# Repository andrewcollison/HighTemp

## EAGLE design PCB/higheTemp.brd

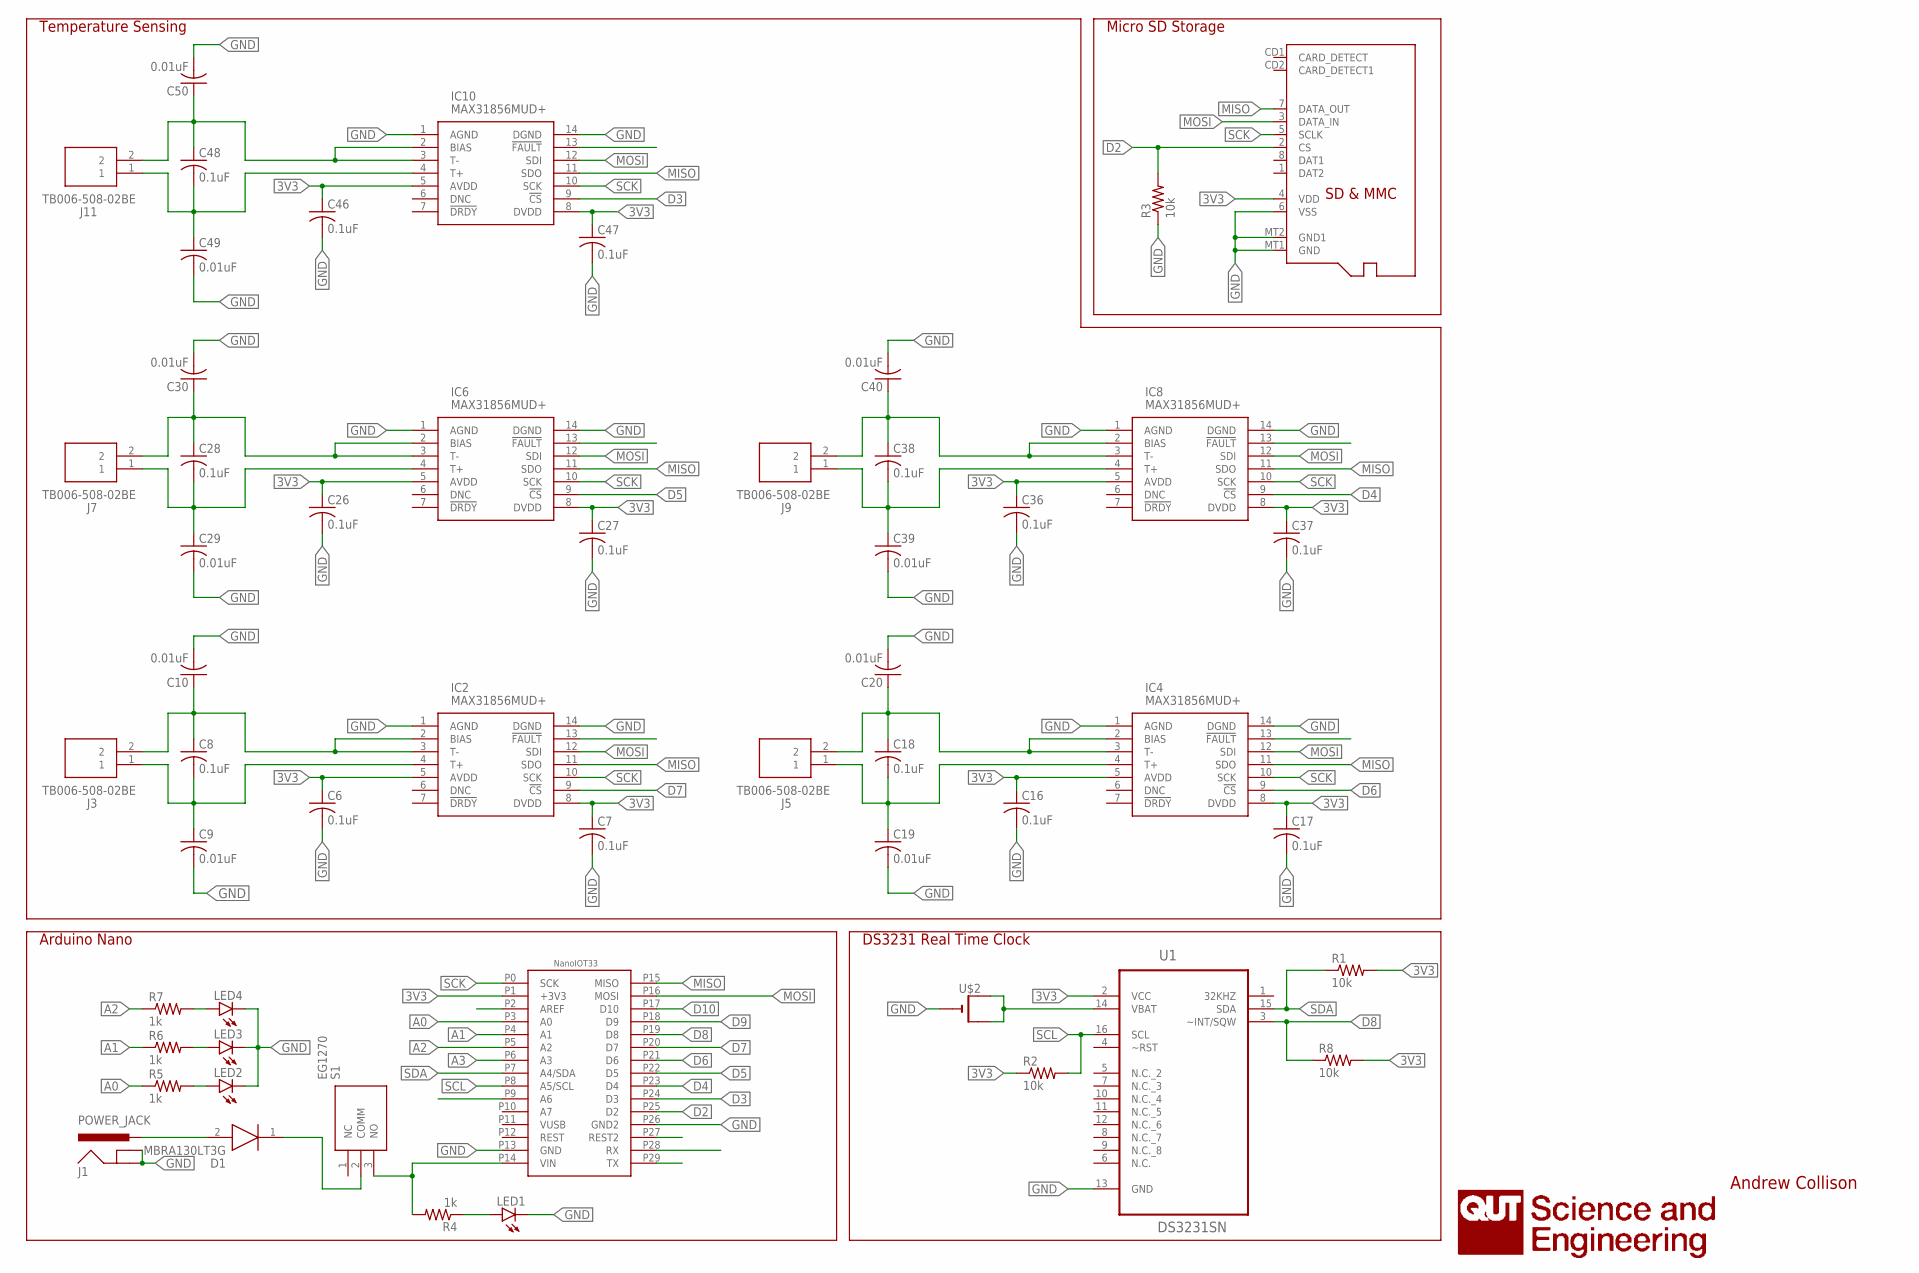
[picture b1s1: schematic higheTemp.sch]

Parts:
C6, C7, C8, C16, C17, C18, C26, C27, C28, C36, C37, C38, C46, C47, C48: 0.1uF; C0603
C9, C10, C19, C20, C29, C30, C39, C40, C49, C50: 0.01uF; C0603
D1: MBRA130LT3G; DIOM5226X220N
IC2, IC4, IC6, IC8, IC10: MAX31856MUD+; SOP65P640X110-14N
J1: POWER_JACK; POWER_JACK_PTH
J3, J5, J7, J9, J11: TB006-508-02BE; TB00650802BE
LED1, LED2, LED3, LED4: LEDCHIPLED_0805; CHIPLED_0805
R1, R2: 10k; R0603
R3, R8: 10k; R0805
R4, R5, R6, R7: 1k; R0603
S1: EG1270
U1: DS3231SN; SOIC127P1032X265-16N
U$1: NANO33IOT
U$2: CR1220SMT; CR1220-SMD
U$3: MICROSD

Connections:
3V3: C6.1, C7.1, C16.1, C17.1, C26.1, C27.1, C36.1, C37.1, C46.1, C47.1, IC2.5 (AVDD), IC2.8 (DVDD), IC4.5 (AVDD), IC4.8 (DVDD), IC6.5 (AVDD), IC6.8 (DVDD), IC8.5 (AVDD), IC8.8 (DVDD), IC10.5 (AVDD), IC10.8 (DVDD), R1.2, R2.1, R8.2, U1.2 (VCC), U$1.P1 (+3V3), U$3.4 (VDD)
A0: R5.1, U$1.P3 (A0)
A1: R6.1, U$1.P4 (A1)
A2: R7.1, U$1.P5 (A2)
A3: U$1.P6 (A3)
D2: R3.2, U$1.P25 (D2), U$3.2 (CS)
D3: IC10.9 (!CS), U$1.P24 (D3)
D4: IC8.9 (!CS), U$1.P23 (D4)
D5: IC6.9 (!CS), U$1.P22 (D5)
D6: IC4.9 (!CS), U$1.P21 (D6)
D7: IC2.9 (!CS), U$1.P20 (D7)
D8: R8.1, U1.3 (~INT/SQW), U$1.P19 (D8)
D9: U$1.P18 (D9)
D10: U$1.P17 (D10)
GND: C6.2, C7.2, C9.2, C10.2, C16.2, C17.2, C19.2, C20.2, C26.2, C27.2, C29.2, C30.2, C36.2, C37.2, C39.2, C40.2, C46.2, C47.2, C49.2, C50.2, IC2.1 (AGND), IC2.14 (DGND), IC4.1 (AGND), IC4.14 (DGND), IC6.1 (AGND), IC6.14 (DGND), IC8.1 (AGND), IC8.14 (DGND), IC10.1 (AGND), IC10.14 (DGND), J1.GND, J1.GNDBREAK, LED1.C, LED2.C, LED3.C, LED4.C, R3.1, U1.13 (GND), U$1.P13 (GND), U$1.P26 (GND2), U$2.-, U$3.6 (VSS), U$3.MT1 (GND), U$3.MT2 (GND1)
MISO: IC2.11 (SDO), IC4.11 (SDO), IC6.11 (SDO), IC8.11 (SDO), IC10.11 (SDO), U$1.P15 (MISO), U$3.7 (DATA_OUT)
MOSI: IC2.12 (SDI), IC4.12 (SDI), IC6.12 (SDI), IC8.12 (SDI), IC10.12 (SDI), U$1.P16 (MOSI), U$3.3 (DATA_IN)
unnamed: U1.14 (VBAT), U$2.+$1 (+), U$2.+$2 (+1)
unnamed: D1.2 (A), J1.PWR
unnamed: LED1.A, R4.1
unnamed: D1.1 (K), S1.2 (COMM)
unnamed: R4.2, S1.3 (NO), U$1.P14 (VIN)
unnamed: LED2.A, R5.2
unnamed: LED4.A, R7.2
unnamed: LED3.A, R6.2
SCK: IC2.10 (SCK), IC4.10 (SCK), IC6.10 (SCK), IC8.10 (SCK), IC10.10 (SCK), U$1.P0 (SCK), U$3.5 (SCLK)
SCL: R2.2, U1.16 (SCL), U$1.P8 (A5/SCL)
SDA: R1.1, U1.15 (SDA), U$1.P7 (A4/SDA)
T1+1: C8.2, C9.1, IC2.4 (T+), J3.1
T1+3: C18.2, C19.1, IC4.4 (T+), J5.1
T1+5: C28.2, C29.1, IC6.4 (T+), J7.1
T1+7: C38.2, C39.1, IC8.4 (T+), J9.1
T1+9: C48.2, C49.1, IC10.4 (T+), J11.1
T1-1: C8.1, C10.1, IC2.2 (BIAS), IC2.3 (T-), J3.2
T1-3: C18.1, C20.1, IC4.2 (BIAS), IC4.3 (T-), J5.2
T1-5: C28.1, C30.1, IC6.2 (BIAS), IC6.3 (T-), J7.2
T1-7: C38.1, C40.1, IC8.2 (BIAS), IC8.3 (T-), J9.2
T1-9: C48.1, C50.1, IC10.2 (BIAS), IC10.3 (T-), J11.2

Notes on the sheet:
Arduino Nano
Temperature Sensing
DS3231 Real Time Clock
Micro SD Storage
Andrew Collison

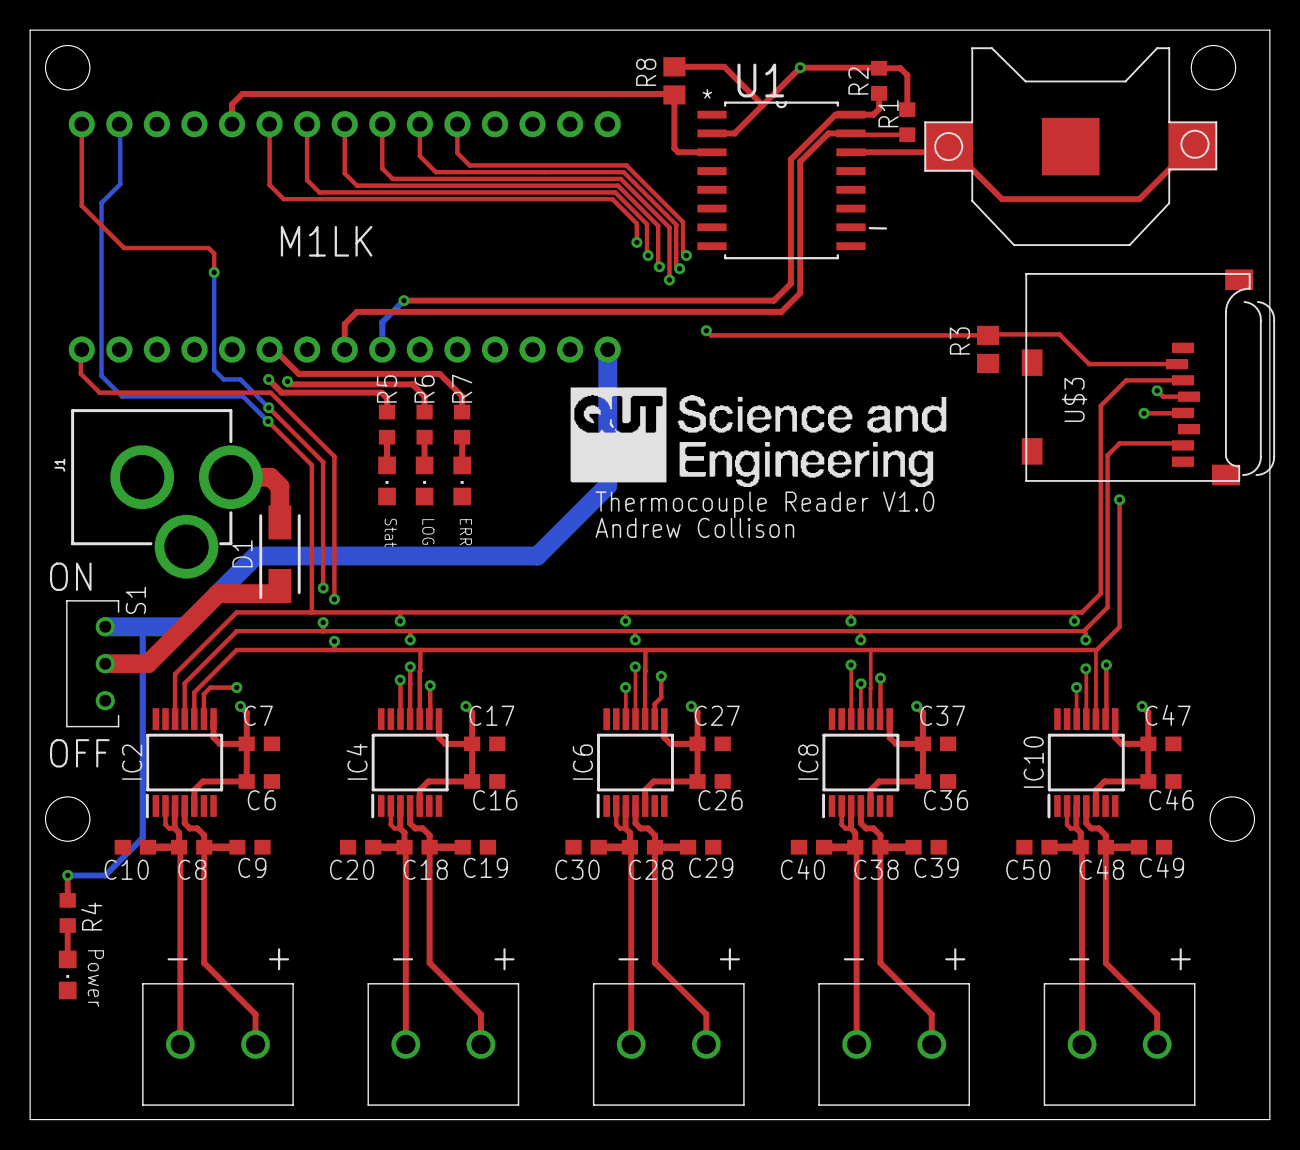
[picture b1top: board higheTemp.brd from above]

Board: 4 copper layers, 83.8 x 73.7 mm, 54 parts (0 on the bottom side), 35 nets.

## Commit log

2020-07-14 Added PCB design files and arduino code for logger
2020-07-14 Added mechanical drawing
    DXF file for the mounting plate that holds a raspberry pi and the high temp PCB
2020-07-15 First Commit
    Added in python code for reading serial port
2020-07-15 Added serial coms for ubuntu
2020-07-15 Updated sensor firmware and python serial
    Added in the 5th channel for the temp logger and re factored the python serial code
2020-07-15 Data vis
    added code to visualise data
2020-07-17 Data acquisition test
    run a couple of tests over night to test stability and reliability
2020-07-20 MQTT Implementation
    Started a new arduino script that publishes the results to an MQTT server. Works on all 5 sensors and is ready for testing in the lab.
2020-07-20 Python MQTT
    Added a python script to read from the mqtt broker
2020-07-20 Ready for lab testing
    Ready to integrate into the system hardware for lab trial
2020-07-21 Lab Setup
    Updated arduino code to work with laboratory network. Setup MQTT for the lab
2020-07-22 Added logging to MQTT messages
    the mqqt python script now logs the data recieved on a topic into a folder for later review
2020-07-24 Visdata Update and Lab Integration
    Updated vis data script to format time and axis labes correctly. successfully integrated system into the e424 lab. Waiting on QUT network connections to allow remote access.
2020-07-29 Slimmed down arduino code
    Removed functions for the rtc and sd card as they are not needed when data is being communicated over mqtt
2020-07-30 Multi channel support
    Added multi channel support for python script
2020-08-11 UI and testing
    Added structure for a database and testing for nod-red dashboard
2020-08-11 Update
    syncing new laptop
2020-09-14 Testing of second temperature sensor
    Made a test file to test sensors without needing to connect to the mqtt server.
    Second sensor is completed and ready for lab integration.
2020-09-15 Documentation
    Started writing documentation for the temp monitoring system.
2020-09-15 Added systemArch.drawio
2020-09-15 Logging
    Updated logging script to compile all topics into a single csv. These are logged with a time stamp.
2020-09-15 Documentation Update
2020-09-15 Pressure Sensor
    Restructure project to include development of a pressure sensor.
2020-09-15 Pressure Sensor Code
    Arduino code written for pressure sensor to integrate into existing mqtt system
2020-11-11 Pressure Testing
    Added a script to test the pressure sensors
2020-11-11 Pressure Testing
    Started arduino code for pressure testing
2020-11-12 Test code
    added all functions to map pressure values with floating point precision
2020-11-12 Pressure Test
    Tested pressure sensors up to 0.130MPa successfully. Data recorded on the arduono is accurate to 0.005MPa. Reading were unstable so will need to take average values.
2020-11-13 Averages and MQTT
    Added function to average reading of the adc accross all the used analogue pins and convert that into pressure. The reading on the arduino and the pressure sensor now line up for the most part. 100 s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
    Also integrated the code into the mqtt frame work so it will work with the node red server in E424.
2020-11-13 Enclosure Design
    File for laser cutting enclosure for pressuresense pcb v1.0
2020-11-13 Deployed Pressure Sensor
    Pressure sensor one is deployed in E424. Is only ready from channel one. Taking the average of 50 samples.
2021-01-09 User Interface
    Started developing the user interface for various sensors
2021-01-09 Serial Interface
    Added in the connection to the serial port and updating the lcd screen with the serial value
2021-01-10 UI Interface
    Serial connection setup, can now enter the comport to connect and it will start printing out the data to the LCD screens
2021-01-19 Pressure Sense
2021-01-21 Ui for raspberry pi touch screen
    Started development of the user interface for the raspberry pi touch screen. Will display data in real time collected from the hightemp and pressure sensors over serial
2021-01-21 Updated serial
    import serial module
2021-01-21 PiUi Update
    Updated ui to have drop down selection for comports. Can now connect and display data on screen from a single comport. Also updated color scheme of UI
2021-01-21 PiUi Update
    added glob
2021-01-21 Update UI
2021-01-24 PiUi
    Updated user interface to include a live graph of data being read out. Added in ui elements for connecting second sensor.
2021-01-26 Package errors
    errors with numpy and pandas packages on the raspberry pi
2021-01-26 Roll back to working
2021-01-26 Roll back 2
2021-01-27 PiUi: Live graph
    Live graph updated to only show set number of data points to prevent memory issues etc. No way to work around showing datetime value on live plot as the package does not support it
2021-01-27 PiUi:Update interface Layout
2021-01-27 PiUi
    Added logging for dual comports. Displays two live plots
2021-02-03 Salt Level Sensor
    Added the spice model for the electronics of the level sensor along with the cad model and stl files for printing.
2021-02-05 Corrosion Monitor
    Added spice simulation files for new corrosion sensor
2021-02-08 Post Process Data
    Small script to visualise data collected from raspberry pi sensor monitor.
2021-02-08 Probe Alignment
    Designed probe alignment jig to keep level sensor probe legs straight
2021-02-24 Level Sensor Code
    Added arduino code for the level sense PCB. Code sends data over serial, error on channel 2 needs further investigation. All other channels working perfectly.
2021-02-25 Central Node
    Started writing code to log data on a central node. Uses multithreading to read all serial ports simultaneously and log them into a txt file. Also has error handling for disconnected com ports. Will 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
2021-02-25 Central Node
    Finalized software for logging data on the central node. Data will be logged to a file based on which comport is connected. Data sent over COM6 will be stored in "Data_COM6.txt".
2021-02-25 Central Node: Error Fix
    Fixed error with package import for use on linux based OS
2021-02-26 Integrated SQL
    Added sql database to central logging node. This will mean the data is both in the database and logged to a .txt file.
2021-03-02 Testing
    Both temperature and and salt level sensors are working and data is being logged to the central logging node. Updated error handling code.
2021-03-03 Quality of Life
    Preparing for handover. Code has been commented and organised into folders. Started to write the documentation for the sensor box thingo
2021-03-04 Change string formatting
    Updated string formatting to handle the unix com port address
2021-03-10 Calibration Data
    Run a calibration test
2021-03-19 Central data node update
    adjust print statements and error messages to declutter the command line
2021-03-19 Updated documentation
    Added wiring diagram for the sodium level sensor to the documentation.

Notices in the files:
parts and their libraries:
SparkFun-Connectors: Licensing: Creative Commons ShareAlike 4.0 International - https://creativecommons.org/licenses/by-sa/4.0
